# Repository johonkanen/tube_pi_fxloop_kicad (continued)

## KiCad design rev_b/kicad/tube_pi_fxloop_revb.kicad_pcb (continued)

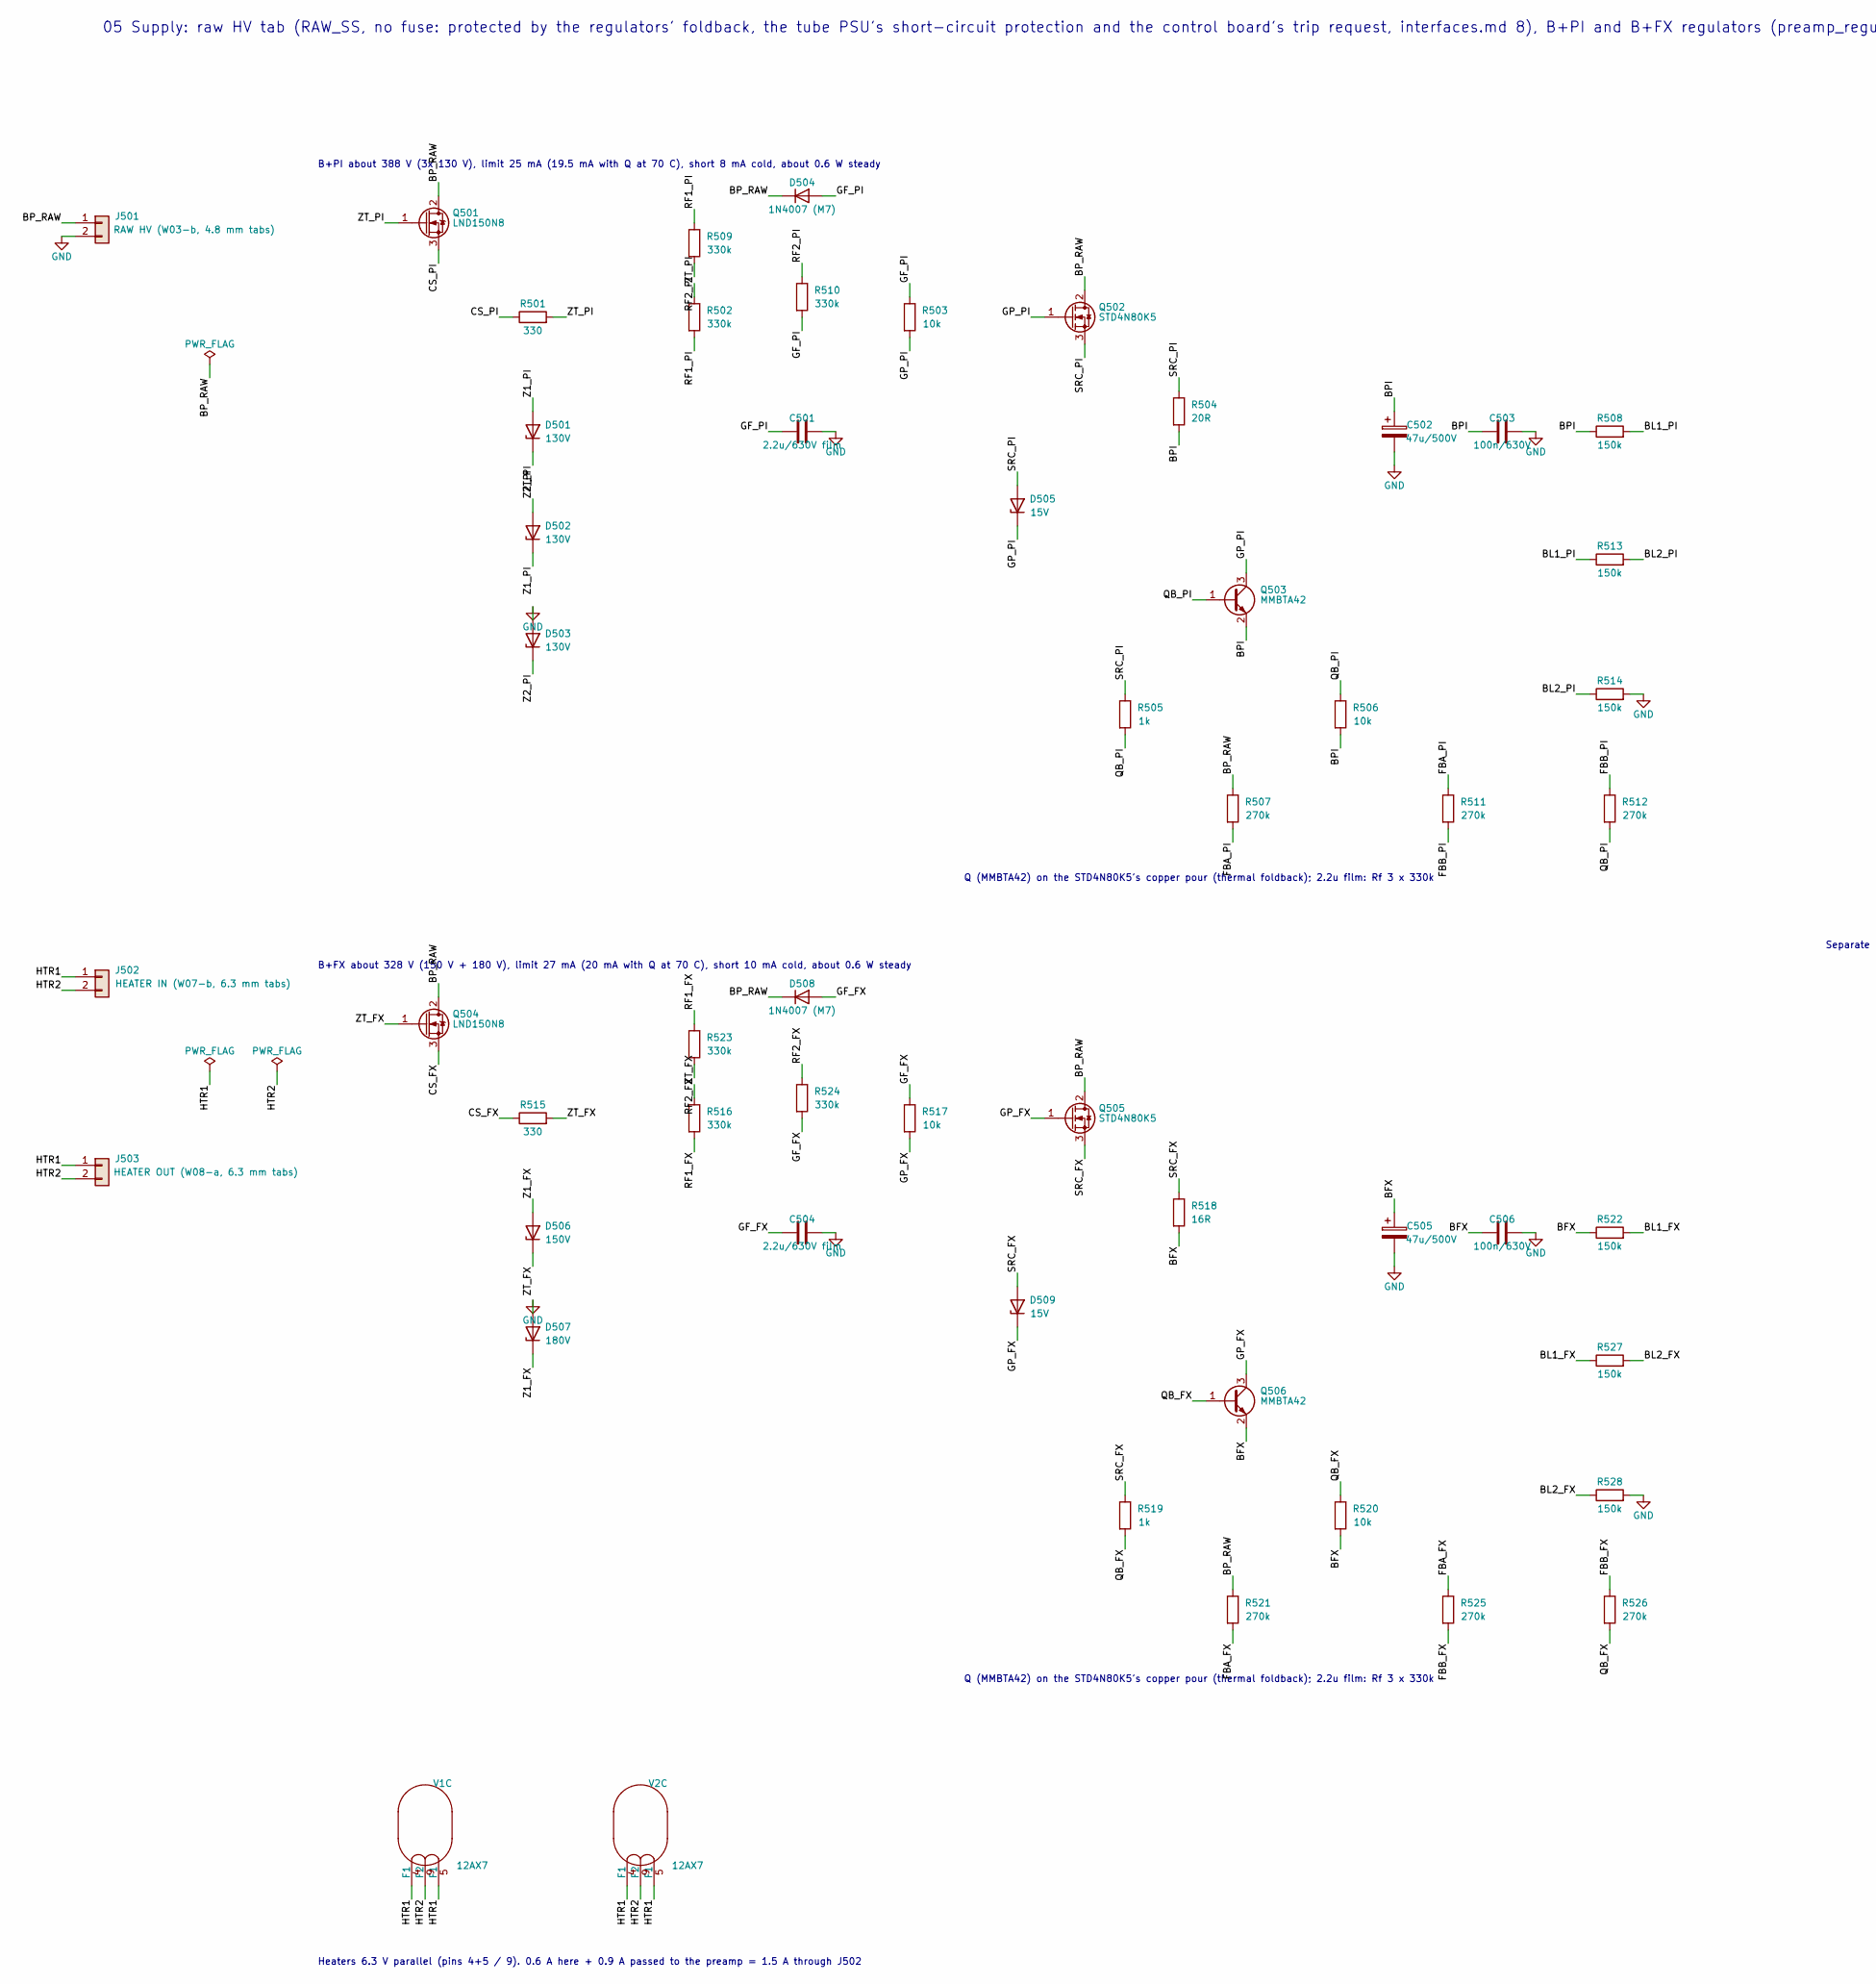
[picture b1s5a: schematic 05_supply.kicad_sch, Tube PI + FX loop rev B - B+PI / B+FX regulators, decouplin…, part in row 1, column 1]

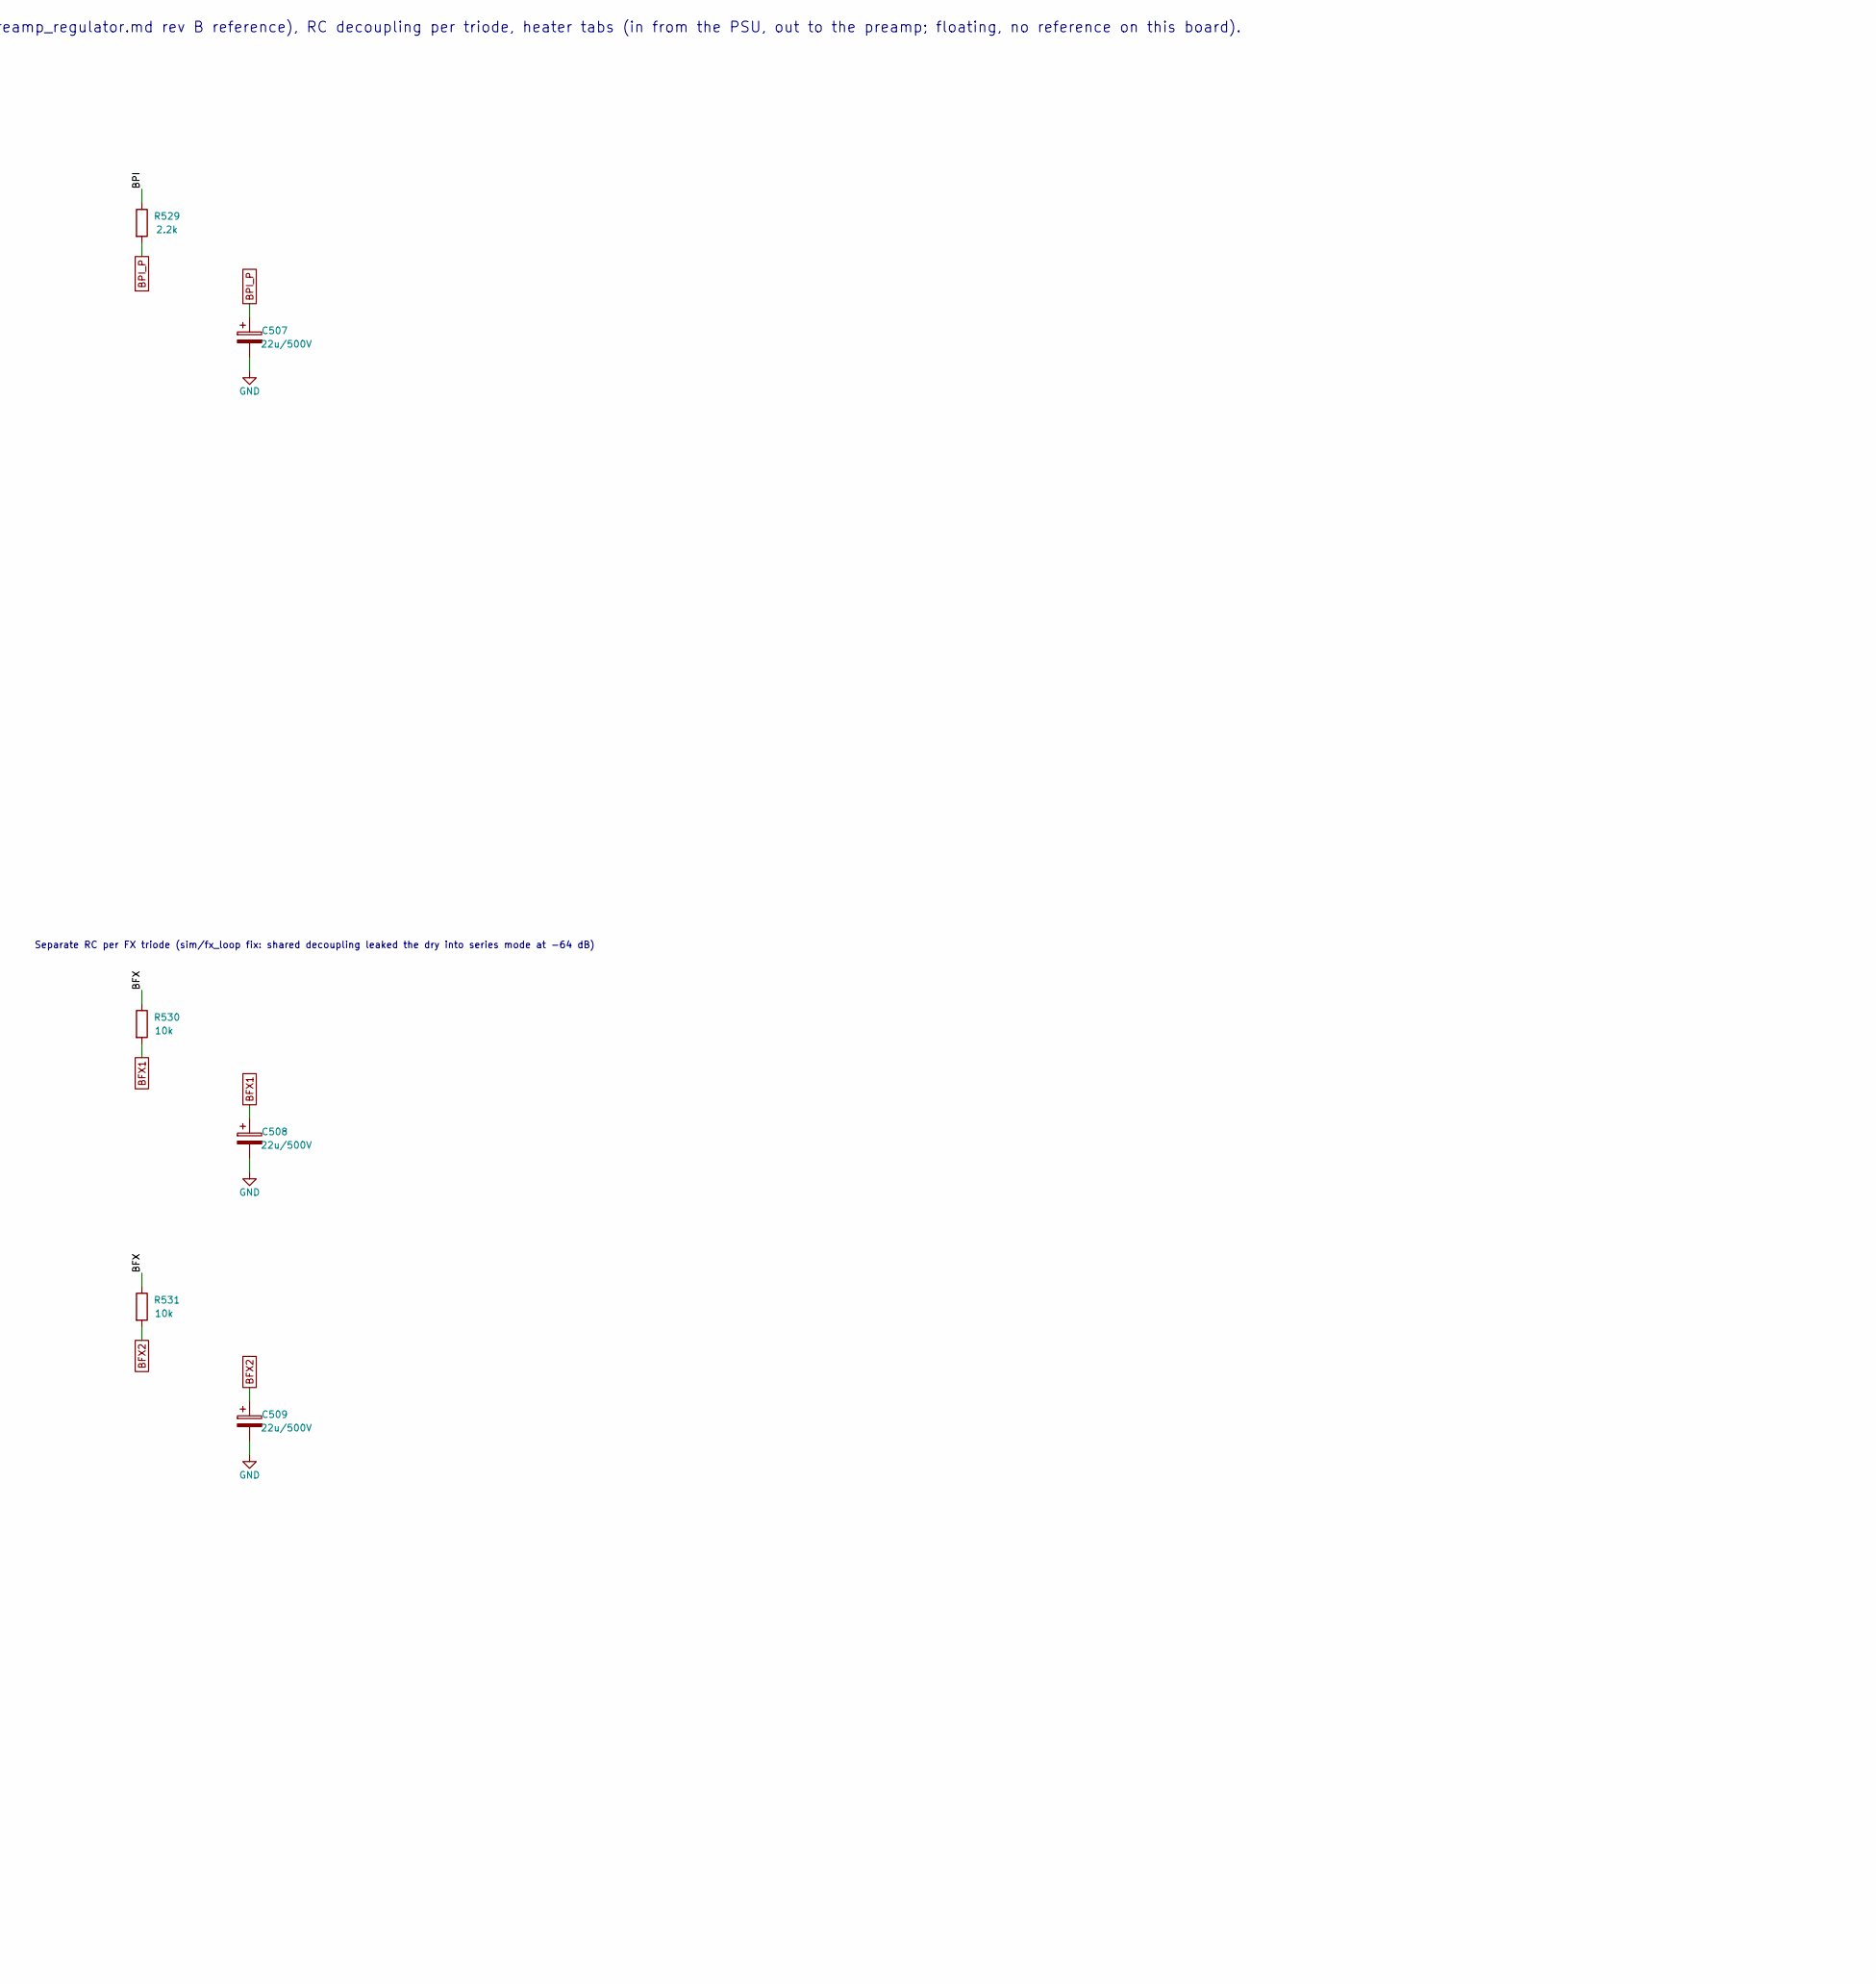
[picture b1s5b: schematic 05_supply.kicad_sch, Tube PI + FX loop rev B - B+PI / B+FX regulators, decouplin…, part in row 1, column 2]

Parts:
C501, C504: 2.2u/630V film; C_Rect_L31.5mm_W17.0mm_P27.50mm_MKS4
C502, C505: 47u/500V; CP_Radial_D18.0mm_P7.50mm
C503, C506: 100n/630V; C_Rect_L13.0mm_W5.0mm_P10.00mm_FKS3_FKP3_MKS4
C507, C508, C509: 22u/500V; CP_Radial_D16.0mm_P7.50mm
D501, D502, D503: 130V; D_SMA
D504, D508: 1N4007 (M7); D_SMA
D505, D509: 15V; D_SOD-123
D506: 150V; D_SMA
D507: 180V; D_SMA
J501: RAW HV (W03-b, 4.8 mm tabs); Faston_Tab_4.8mm_x2_P15.00mm
J502: HEATER IN (W07-b, 6.3 mm tabs); Faston_Tab_6.3mm_x2_P12.70mm
J503: HEATER OUT (W08-a, 6.3 mm tabs); Faston_Tab_6.3mm_x2_P12.70mm
Q501, Q504: LND150N8; SOT-89-3
Q502, Q505: STD4N80K5; TO-252-2
Q503, Q506: MMBTA42; SOT-23
R501, R515: 330; R_1206_3216Metric
R502, R509, R510, R516, R523, R524: 330k; R_2512_6332Metric
R503, R506, R517, R520, R530, R531: 10k; R_1206_3216Metric
R504: 20R; R_1206_3216Metric
R505, R519: 1k; R_1206_3216Metric
R507, R511, R512, R521, R525, R526: 270k; R_2512_6332Metric
R508, R513, R514, R522, R527, R528: 150k; R_2512_6332Metric
R518: 16R; R_1206_3216Metric
R529: 2.2k; R_1206_3216Metric
V1: 12AX7; Valve_Noval_Belton_PCD21.00mm
V2: 12AX7; Valve_Noval_Belton_PCD21.00mm_Pin6_3.8mm

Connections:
/05 B+PI and B+FX regulators, decoupling, heaters, power tabs/BFX: C505.1, C506.1, Q506.2 (E), R518.2, R520.2, R522.1, R530.1, R531.1
/05 B+PI and B+FX regulators, decoupling, heaters, power tabs/BL1_FX: R522.2, R527.1
/05 B+PI and B+FX regulators, decoupling, heaters, power tabs/BL1_PI: R508.2, R513.1
/05 B+PI and B+FX regulators, decoupling, heaters, power tabs/BL2_FX: R527.2, R528.1
/05 B+PI and B+FX regulators, decoupling, heaters, power tabs/BL2_PI: R513.2, R514.1
/05 B+PI and B+FX regulators, decoupling, heaters, power tabs/BPI: C502.1, C503.1, Q503.2 (E), R504.2, R506.2, R508.1, R529.1
/05 B+PI and B+FX regulators, decoupling, heaters, power tabs/BP_RAW: D504.1 (K), D508.1 (K), J501.1, Q501.2 (D), Q502.2 (D), Q504.2 (D), Q505.2 (D), R507.1, R521.1
/05 B+PI and B+FX regulators, decoupling, heaters, power tabs/CS_FX: Q504.3 (S), R515.1
/05 B+PI and B+FX regulators, decoupling, heaters, power tabs/CS_PI: Q501.3 (S), R501.1
/05 B+PI and B+FX regulators, decoupling, heaters, power tabs/FBA_FX: R521.2, R525.1
/05 B+PI and B+FX regulators, decoupling, heaters, power tabs/FBA_PI: R507.2, R511.1
/05 B+PI and B+FX regulators, decoupling, heaters, power tabs/FBB_FX: R525.2, R526.1
/05 B+PI and B+FX regulators, decoupling, heaters, power tabs/FBB_PI: R511.2, R512.1
/05 B+PI and B+FX regulators, decoupling, heaters, power tabs/GF_FX: C504.1, D508.2 (A), R517.1, R524.2
/05 B+PI and B+FX regulators, decoupling, heaters, power tabs/GF_PI: C501.1, D504.2 (A), R503.1, R510.2
/05 B+PI and B+FX regulators, decoupling, heaters, power tabs/GP_FX: D509.1 (K), Q505.1 (G), Q506.3 (C), R517.2
/05 B+PI and B+FX regulators, decoupling, heaters, power tabs/GP_PI: D505.1 (K), Q502.1 (G), Q503.3 (C), R503.2
/05 B+PI and B+FX regulators, decoupling, heaters, power tabs/HTR1: J502.1, J503.1, V1.4 (F1), V1.5 (F1), V2.4 (F1), V2.5 (F1)
/05 B+PI and B+FX regulators, decoupling, heaters, power tabs/HTR2: J502.2, J503.2, V1.9 (F2), V2.9 (F2)
/05 B+PI and B+FX regulators, decoupling, heaters, power tabs/QB_FX: Q506.1 (B), R519.2, R520.1, R526.2
/05 B+PI and B+FX regulators, decoupling, heaters, power tabs/QB_PI: Q503.1 (B), R505.2, R506.1, R512.2
/05 B+PI and B+FX regulators, decoupling, heaters, power tabs/RF1_FX: R516.2, R523.1
/05 B+PI and B+FX regulators, decoupling, heaters, power tabs/RF1_PI: R502.2, R509.1
/05 B+PI and B+FX regulators, decoupling, heaters, power tabs/RF2_FX: R523.2, R524.1
/05 B+PI and B+FX regulators, decoupling, heaters, power tabs/RF2_PI: R509.2, R510.1
/05 B+PI and B+FX regulators, decoupling, heaters, power tabs/SRC_FX: D509.2 (A), Q505.3 (S), R518.1, R519.1
/05 B+PI and B+FX regulators, decoupling, heaters, power tabs/SRC_PI: D505.2 (A), Q502.3 (S), R504.1, R505.1
/05 B+PI and B+FX regulators, decoupling, heaters, power tabs/Z1_FX: D506.2 (A), D507.1 (K)
/05 B+PI and B+FX regulators, decoupling, heaters, power tabs/Z1_PI: D501.2 (A), D502.1 (K)
/05 B+PI and B+FX regulators, decoupling, heaters, power tabs/Z2_PI: D502.2 (A), D503.1 (K)
/05 B+PI and B+FX regulators, decoupling, heaters, power tabs/ZT_FX: D506.1 (K), Q504.1 (G), R515.2, R516.1
/05 B+PI and B+FX regulators, decoupling, heaters, power tabs/ZT_PI: D501.1 (K), Q501.1 (G), R501.2, R502.1
BFX1: C508.1, R530.2; also elsewhere on the board
BFX2: C509.1, R531.2; also elsewhere on the board
BPI_P: C507.1, R529.2; also elsewhere on the board
GND: C501.2, C502.2, C503.2, C504.2, C505.2, C506.2, C507.2, C508.2, C509.2, D503.2 (A), D507.2 (A), J501.2, R514.2, R528.2; also elsewhere on the board

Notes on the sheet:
05 Supply: raw HV tab (RAW_SS, no fuse: protected by the regulators' foldback, the tube PSU's short-circuit protection and the control board's trip request, interfaces.md 8), B+PI and B+FX regulators (preamp_regulator.md rev B reference), RC decoupling per triode, heater tabs (in from the PSU, out 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
B+PI about 388 V (3x 130 V), limit 25 mA (19.5 mA with Q at 70 C), short 8 mA cold, about 0.6 W steady
Q (MMBTA42) on the STD4N80K5's copper pour (thermal foldback); 2.2u film: Rf 3 x 330k
B+FX about 328 V (150 V + 180 V), limit 27 mA (20 mA with Q at 70 C), short 10 mA cold, about 0.6 W steady
Separate RC per FX triode (sim/fx_loop fix: shared decoupling leaked the dry into series mode at -64 dB)
Heaters 6.3 V parallel (pins 4+5 / 9). 0.6 A here + 0.9 A passed to the preamp = 1.5 A through J502

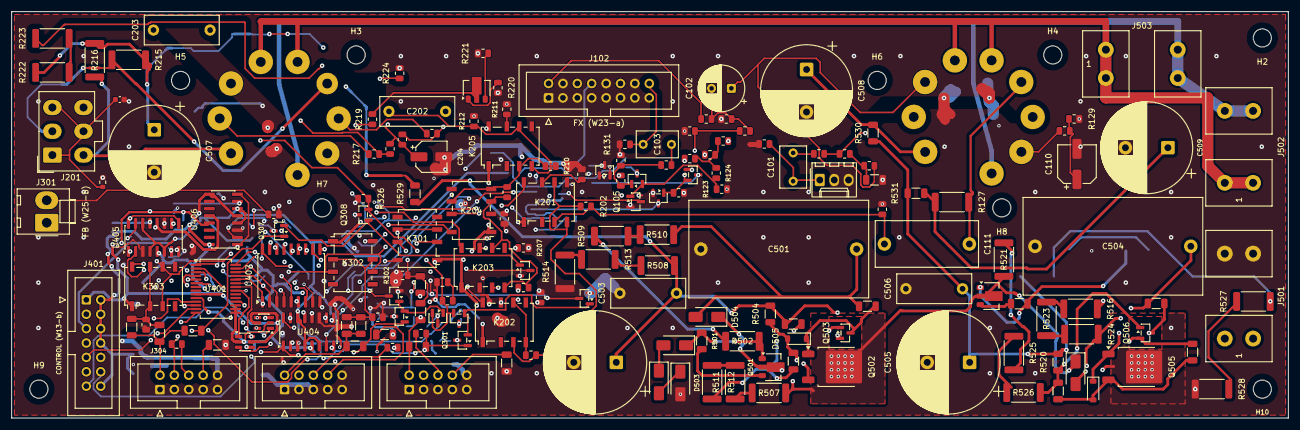
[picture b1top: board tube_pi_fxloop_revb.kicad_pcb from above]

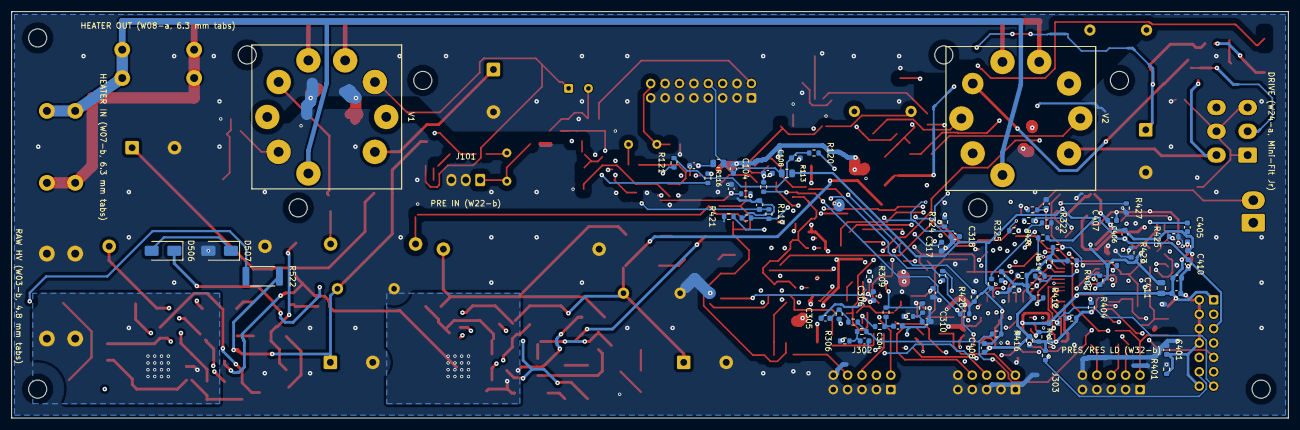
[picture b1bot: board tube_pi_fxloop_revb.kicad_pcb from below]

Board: 4 copper layers, 225.4 x 71.8 mm, 261 parts (81 on the bottom side), 168 nets.

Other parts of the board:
H2, H3, H4, H5, H6, H7, H8, H9, H10: M3 (3.2 NPTH, no net); MountingHole_3.2mm_M3

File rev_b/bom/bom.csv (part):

Qty,Refs,Value,Footprint,Candidate MPN,LCSC,DNP,Note
1,C101,100n/250V film,Capacitor_THT:C_Rect_L7.2mm_W4.5mm_P5.00mm_FKS2_FKP2_MKS2_MKP2,,,,film >= 100 V (PET / PP)
1,C102,4.7u/160V,Capacitor_THT:CP_Radial_D8.0mm_P3.50mm,,,,105 C electrolytic
1,C103,220n/100V film,Capacitor_THT:C_Rect_L7.2mm_W4.5mm_P5.00mm_FKS2_FKP2_MKS2_MKP2,,,,film >= 100 V (PET / PP)
12,C104 C201 C401 C402 C403 C404 C405 C406 C407 C408 C409 C410,100n,Capacitor_SMD:C_0603_1608Metric,CC0603KRX7R9BB104,C14663,,
14,C105 C106 C107 C108 C109 C304 C305 C306 C310 C311 C312 C316 C317 C318,10n,Capacitor_SMD:C_0603_1608Metric,0603B103K500NT,C57112,,
1,C110,100u/25V,Capacitor_SMD:CP_Elec_6.3x7.7,,,,105 C electrolytic
1,C111,470n/400V film,Capacitor_THT:C_Rect_L18.0mm_W8.0mm_P15.00mm_FKS3_FKP3,CBB21-400V474JP15,C2888194,,film >= 400 V
1,C202,10n/630V film,Capacitor_THT:C_Rect_L13.0mm_W5.0mm_P10.00mm_FKS3_FKP3_MKS4,,,,film 630 V
1,C203,22n/630V film,Capacitor_THT:C_Rect_L13.0mm_W5.0mm_P10.00mm_FKS3_FKP3_MKS4,MPE223J2JB050C030ZR,C53224144,,film 630 V
1,C204,10u/50V,Capacitor_SMD:CP_Elec_5x5.4,,,,105 C electrolytic
3,C301 C307 C313,22p/200V C0G (PI-6),Capacitor_SMD:C_1206_3216Metric,,,,
6,C302 C303 C308 C309 C314 C315,22n C0G 50V,Capacitor_SMD:C_1206_3216Metric,C1206N223K050T,C105982,,
1,C319,DNP (step C),Capacitor_SMD:C_0805_2012Metric,,,yes,
1,C411,10u/16V,Capacitor_SMD:C_0805_2012Metric,,,,
2,C501 C504,2.2u/630V film,Capacitor_THT:C_Rect_L31.5mm_W17.0mm_P27.50mm_MKS4,,,,PP film 630 V (preamp_regulator.md)
2,C502 C505,47u/500V,Capacitor_THT:CP_Radial_D18.0mm_P7.50mm,"Nichicon UCY2H470MHD6 (18 x 31.5, P7.5; alt. Rubycon 500LXW47MEFR18X25)",,,"105 C, 12000 h, not at LCSC: hand-solder"
2,C503 C506,100n/630V,Capacitor_THT:C_Rect_L13.0mm_W5.0mm_P10.00mm_FKS3_FKP3_MKS4,CBB21-630V104JP10,C2888191,,film 630 V
3,C507 C508 C509,22u/500V,Capacitor_THT:CP_Radial_D16.0mm_P7.50mm,"Nichicon UCY2H220MHD6 (16 x 25, P7.5)",,,"105 C, 12000 h, not at LCSC: hand-solder"
3,D501 D502 D503,130V,Diode_SMD:D_SMA,1SMA5952B,C48578686,,
2,D504 D508,1N4007 (M7),Diode_SMD:D_SMA,M7,C7420350,,
2,D505 D509,15V,Diode_SMD:D_SOD-123,BZT52C15,C2891782,,
1,D506,150V,Diode_SMD:D_SMA,1SMA5953B,,,
1,D507,180V,Diode_SMD:D_SMA,1SMA5955B,,,
1,J101,PRE IN (W22-b),Connector_Molex:Molex_KK-254_AE-6410-03A_1x03_P2.54mm_Vertical,Molex 22272031,C471416,,
1,J102,FX (W23-a),Connector_IDC:IDC-Header_2x08_P2.54mm_Vertical,,,,
1,J201,"DRIVE (W24-a, Mini-Fit Jr)",Connector_Molex:Molex_Mini-Fit_Jr_5566-06A_2x03_P4.20mm_Vertical,"Molex 39-28-1063 class (5566-06A; confirm the order code), receptacle 39-01-2060",,,"W24: Mini-Fit Jr 600 V (V5); 2x3 with position 6 unused, same mapping on the power amp"
1,J301,FB (W25-b),Connector_Molex:Molex_KK-396_A-41791-0002_1x02_P3.96mm_Vertical,,,,
1,J302,PRES/RES CL (W30-b),Connector_IDC:IDC-Header_2x05_P2.54mm_Vertical,,,,
1,J303,PRES/RES CR (W31-b),Connector_IDC:IDC-Header_2x05_P2.54mm_Vertical,,,,
1,J304,PRES/RES LD (W32-b),Connector_IDC:IDC-Header_2x05_P2.54mm_Vertical,,,,
1,J401,CONTROL (W13-b),Connector_IDC:IDC-Header_2x07_P2.54mm_Vertical,HY2541WV-N-2x7P,C17179454,,
1,J501,"RAW HV (W03-b, 4.8 mm tabs)",tube_pi_fxloop_revb:PLACEHOLDER_Tab_x2_4.8mm_Legs_P5.00mm_D1.4mm,2x BTC-3-PCB484608T,C20626099,,PLACEHOLDER footprint
1,J502,"HEATER IN (W07-b, 6.3 mm tabs)",tube_pi_fxloop_revb:PLACEHOLDER_Tab_x2_6.3mm_Legs_P5.00mm_D1.4mm,2x BTC-3-PCB485005D,C20626100,,PLACEHOLDER footprint
1,J503,"HEATER OUT (W08-a, 6.3 mm tabs)",tube_pi_fxloop_revb:PLACEHOLDER_Tab_x2_6.3mm_Legs_P5.00mm_D1.4mm,2x BTC-3-PCB485005D,C20626100,,PLACEHOLDER footprint
8,K201 K202 K203 K204 K205 K301 K302 K303,G6K-2F-Y 5VDC,Relay_SMD:Relay_DPDT_Omron_G6K-2F-Y,G6K-2F-Y-TR DC5,C47190,,"coil + 1 / - 8; NC 4 / 5, NO 2 / 7 (Omron datasheet)"
14,Q101 Q102 Q103 Q104 Q105 Q301 Q302 Q303 Q304 Q305 Q306 Q307 Q308 Q309,MMBFJ113,Package_TO_SOT_SMD:SOT-23,MMBFJ113,C891686,,
1,Q201,DN2540N8,Package_TO_SOT_SMD:SOT-89-3,DN2540N8-G,,,
2,Q501 Q504,LND150N8,Package_TO_SOT_SMD:SOT-89-3,LND150N8-G,C629123,,
2,Q502 Q505,STD4N80K5,Package_TO_SOT_SMD:TO-252-2,STD4N80K5,C472540,,DPAK on a copper pour; Q MMBTA42 on the same pour (thermal foldback)
2,Q503 Q506,MMBTA42,Package_TO_SOT_SMD:SOT-23,MMBTA42,C20069138,,
2,R101 R131,2.2M,Resistor_SMD:R_0805_2012Metric,0805W8F2204T5E,,,
3,R102 R109 R326,4.7k,Resistor_SMD:R_0805_2012Metric,0805W8F4701T5E,,,
12,R103 R106 R111 R113 R118 R123 R130 R213 R218 R302 R310 R318,1M,Resistor_SMD:R_0805_2012Metric,0805W8F1004T5E,C17514,,
1,R104,1.5k,Resistor_SMD:R_0805_2012Metric,0805W8F1501T5E,,,
1,R105,22k 0.5W,Resistor_SMD:R_1206_3216Metric,1206W4F2202T5E,,,
8,R107 R126 R214 R217 R219 R304 R312 R320,1k,Resistor_SMD:R_0805_2012Metric,0805W8F1001T5E,,,
1,R108,47k,Resistor_SMD:R_0805_2012Metric,0805W8F4702T5E,,,
5,R110 R114 R119 R124 R224,100k,Resistor_SMD:R_0805_2012Metric,0805W8F1003T5E,C149504,,
1,R112,11k,Resistor_SMD:R_0805_2012Metric,0805W8F1102T5E,,,
38,R115 R117 R120 R122 R305 R307 R309 R313 R315 R317 R321 R323 R325 R403 R404 R405 R406 R407 R408 R409 R410 R411 R412 R413 R414 R415 R416 R417 R418 R419 R420 R421 R422 R423 R424 R425 R426 R427,100k,Resistor_SMD:R_0603_1608Metric,0603WAF1003T5E,C25803,,
8,R116 R121 R306 R308 R314 R316 R322 R324,1M,Resistor_SMD:R_0603_1608Metric,0603WAF1004T5E,,,
1,R125,220k,Resistor_SMD:R_0805_2012Metric,0805W8F2203T5E,C17556,,
1,R127,100k,Resistor_SMD:R_2512_6332Metric,FRC2512F1003TS,C2934045,,"2512, 1 W, 200 V"
1,R128,680,Resistor_SMD:R_0805_2012Metric,0805W8F6800T5E,,,
1,R129,820,Resistor_SMD:R_0805_2012Metric,0805W8F8200T5E,,,
2,R201 R401,10R,Resistor_SMD:R_0603_1608Metric,0603WAF100JT5E,C22859,,
1,R202,5.36k,Resistor_SMD:R_0805_2012Metric,0805W8F5361T5E,,,
1,R203,412k,Resistor_SMD:R_0805_2012Metric,0805W8F4123T5E,,,
1,R204,10.2k,Resistor_SMD:R_0805_2012Metric,0805W8F1022T5E,,,
1,R205,191k,Resistor_SMD:R_0805_2012Metric,0805W8F1913T5E,,,
1,R206,18.2k,Resistor_SMD:R_0805_2012Metric,0805W8F1822T5E,,,
1,R207,84.5k,Resistor_SMD:R_0805_2012Metric,0805W8F8452T5E,,,
1,R208,30.1k,Resistor_SMD:R_0805_2012Metric,0805W8F3012T5E,,,
1,R209,33.2k,Resistor_SMD:R_0805_2012Metric,0805W8F3322T5E,,,
1,R210,42.2k,Resistor_SMD:R_0805_2012Metric,0805W8F4222T5E,,,
1,R211,7.87k,Resistor_SMD:R_0805_2012Metric,0805W8F7871T5E,,,
1,R212,49.9k,Resistor_SMD:R_0805_2012Metric,0805W8F4992T5E,,,
2,R215 R216,100k 1W,Resistor_SMD:R_2512_6332Metric,25121WF1003T4E,,,"2512, 1 W, 200 V"
1,R220,100,Resistor_SMD:R_0805_2012Metric,0805W8F1000T5E,,,
1,R221,"1k (select, ~2 mA)",Resistor_SMD:R_0805_2012Metric,0805W8F1001T5E,,,
2,R222 R223,820k,Resistor_SMD:R_2512_6332Metric,25121WF8203T4E,,,"2512, 1 W, 200 V"
1,R301,0R,Resistor_SMD:R_0805_2012Metric,0805W8F0000T5E,,,
3,R303 R311 R319,100k 0.5W,Resistor_SMD:R_1206_3216Metric,1206W4F1003T5E,,,
1,R327,DNP (step R),Resistor_SMD:R_0805_2012Metric,,,yes,
1,R402,10k,Resistor_SMD:R_0603_1608Metric,0603WAF1002T5E,C25804,,
2,R501 R515,330,Resistor_SMD:R_1206_3216Metric,FRC1206F3300TS,C2933675,,
6,R502 R509 R510 R516 R523 R524,330k,Resistor_SMD:R_2512_6332Metric,25121WF3303T4E,,,"2512, 1 W, 200 V"
6,R503 R506 R517 R520 R530 R531,10k,Resistor_SMD:R_1206_3216Metric,1206W4F1002T5E,C17902,,
1,R504,20R,Resistor_SMD:R_1206_3216Metric,1206 20R 1 % thick film,,,
2,R505 R519,1k,Resistor_SMD:R_1206_3216Metric,1206W4F1001T5E,C4410,,
6,R507 R511 R512 R521 R525 R526,270k,Resistor_SMD:R_2512_6332Metric,CL2512FN270KB,C48392179,,"2512, 1 W, 200 V"
6,R508 R513 R514 R522 R527 R528,150k,Resistor_SMD:R_2512_6332Metric,25121WF1503T4E,,,"2512, 1 W, 200 V"
1,R518,16R,Resistor_SMD:R_1206_3216Metric,1206 16R 1 % thick film,,,
1,R529,2.2k,Resistor_SMD:R_1206_3216Metric,1206W4F2201T5E,,,
1,U401,MCP23S17-E/SS,Package_SO:SSOP-28_5.3x10.2mm_P0.65mm,MCP23S17-E/SS,C148009,,
2,U402 U403,74LVC1G11,Package_TO_SOT_SMD:SOT-23-6,"74LVC1G11GV,125",,,
3,U404 U405 U406,DG412DY,Package_SO:SOIC-16_3.9x9.9mm_P1.27mm,DG412DY-T1-E3,C553989,,
1,U407,ULN2803A,Package_SO:SOIC-18W_7.5x11.6mm_P1.27mm,ULN2803ADWR,,,check the 70 C design temperature against the bought part's rating (ENV-2)
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
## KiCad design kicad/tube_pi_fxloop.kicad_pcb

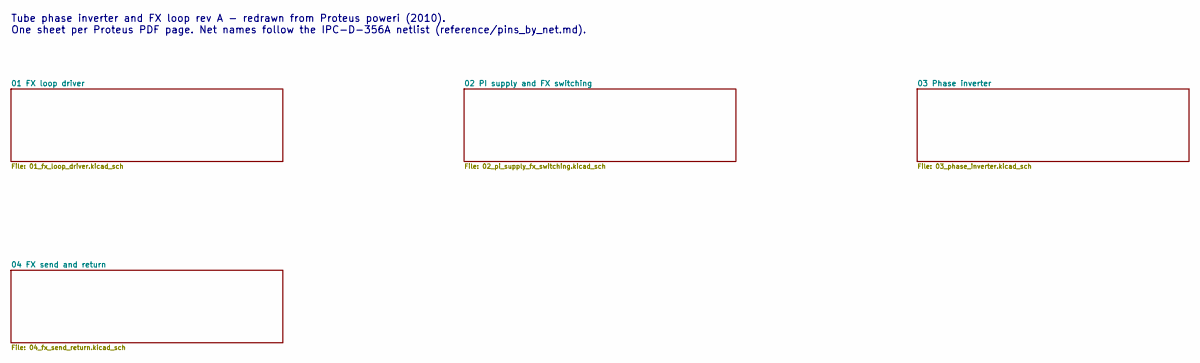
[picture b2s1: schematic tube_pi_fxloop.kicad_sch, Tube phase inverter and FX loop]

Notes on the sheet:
Tube phase inverter and FX loop rev A - redrawn from Proteus poweri (2010). One sheet per Proteus PDF page. Net names follow the IPC-D-356A netlist (reference/pins_by_net.md).

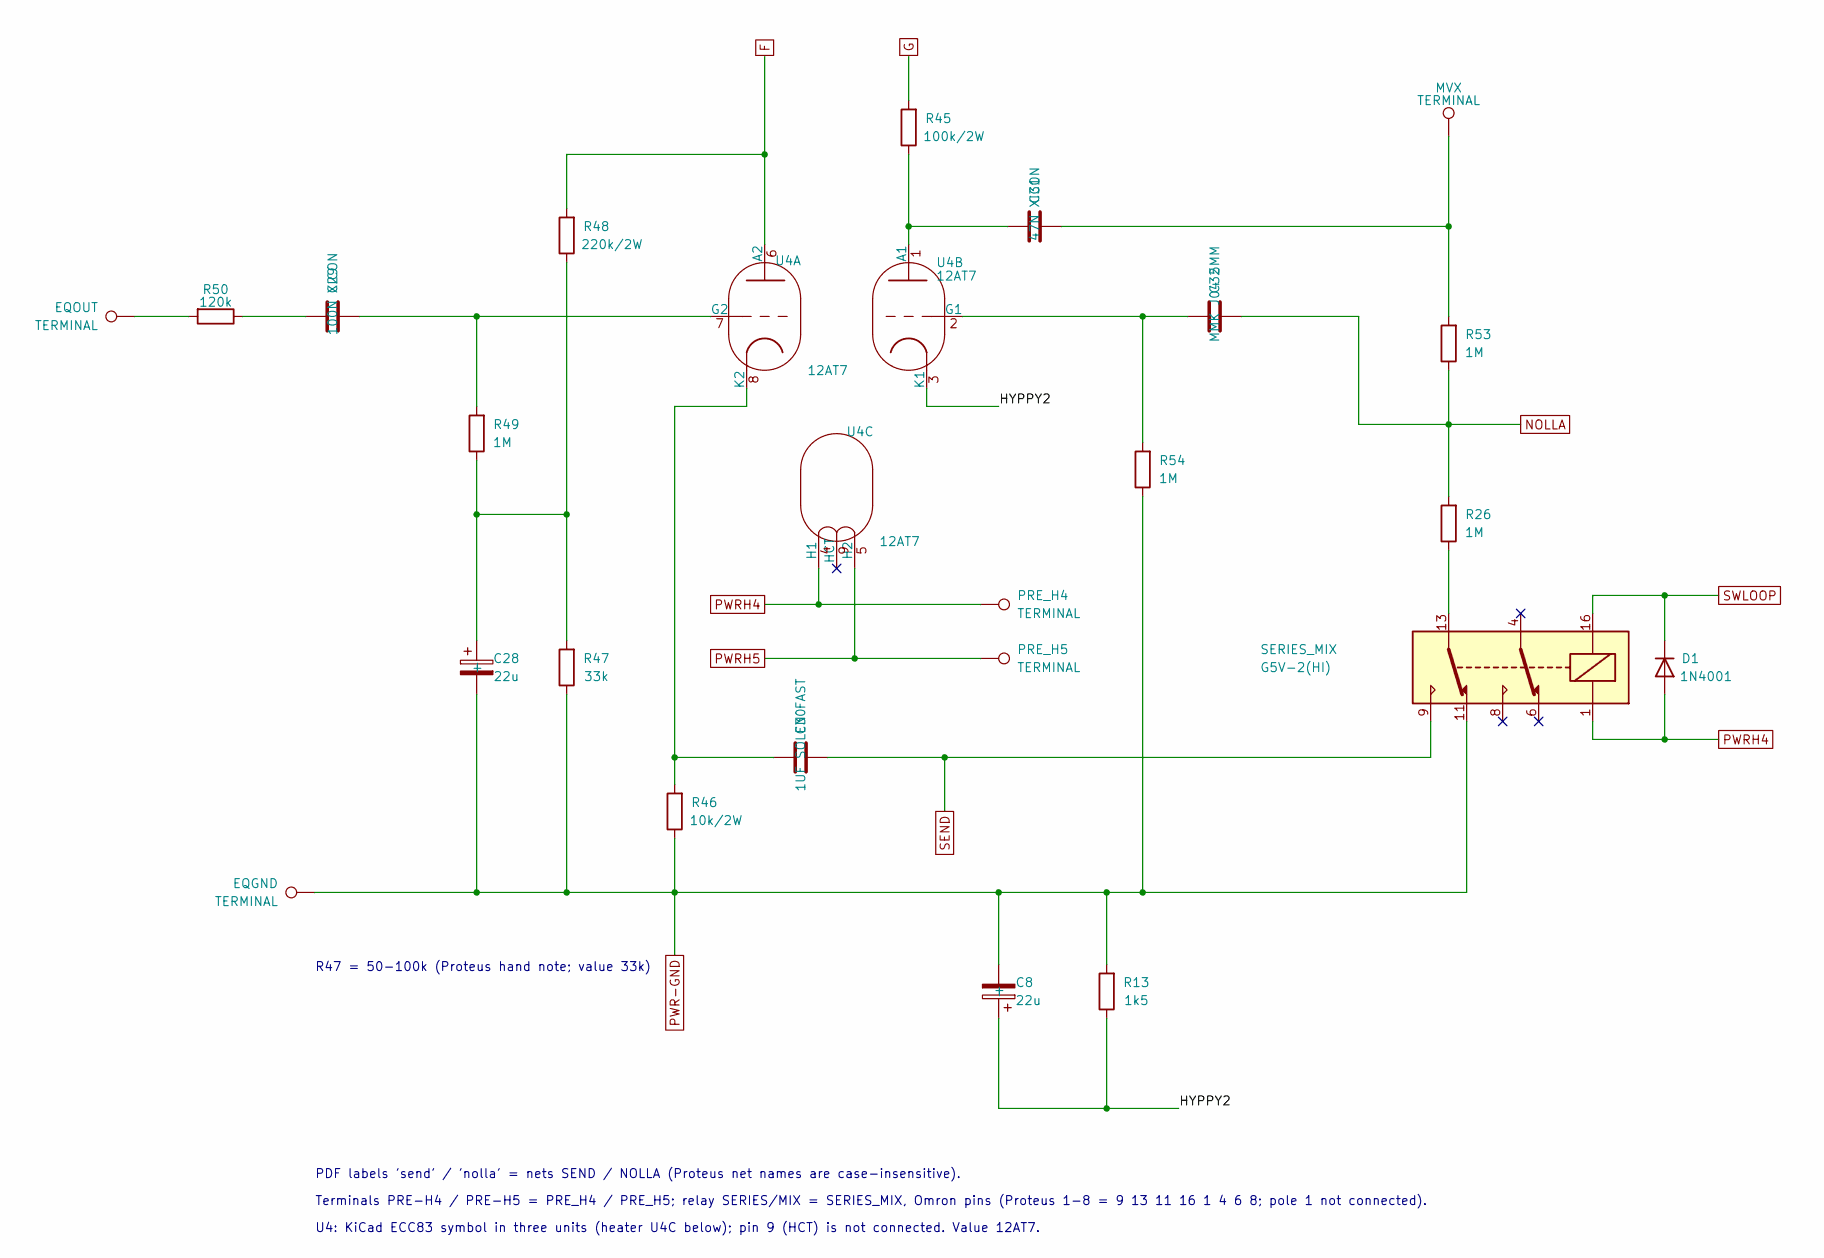
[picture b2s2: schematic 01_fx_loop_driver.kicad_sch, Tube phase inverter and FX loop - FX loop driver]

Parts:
C8, C28: 22u; CP_Radial_D5.0mm_P2.54mm_PM
C29: 100N XICON; C_Rect_L23.1mm_W6.0mm_P20.00mm
C30: 1UF SOLEN FAST; C_Axial_L26.7mm_D15.2mm_P30.48mm_Horizontal
C31: 47N XICON; C_Rect_L18.0mm_W6.0mm_P15.00mm_FKS3_FKP3
C32: MMK J04 5MM; C_Rect_L7.2mm_W5.0mm_P5.00mm
D1: 1N4001; D_DO-41_SOD81_P10.16mm_Horizontal_AK
EQGND: TERMINAL; FlyLead_Pad_D3.048mm_Drill1.524mm
EQOUT: TERMINAL; FlyLead_Pad_D3.048mm_Drill1.524mm
MVX: TERMINAL; FlyLead_Pad_D3.048mm_Drill1.524mm
PRE_H4, PRE_H5: TERMINAL; FlyLead_Pad_D3.048mm_Drill1.524mm
R13: 1k5; R_Axial_DIN0207_L6.3mm_D2.5mm_P10.16mm_Horizontal
R26, R49, R53, R54: 1M; R_Axial_DIN0207_L6.3mm_D2.5mm_P10.16mm_Horizontal
R45: 100k/2W; R_Axial_DIN0414_L11.9mm_D4.5mm_P19.05mm_Horizontal
R46: 10k/2W; R_Axial_DIN0414_L11.9mm_D4.5mm_P19.05mm_Horizontal
R47: 33k; R_Axial_DIN0207_L6.3mm_D2.5mm_P10.16mm_Horizontal
R48: 220k/2W; R_Axial_DIN0414_L11.9mm_D4.5mm_P19.05mm_Horizontal
R50: 120k; R_Axial_DIN0207_L6.3mm_D2.5mm_P10.16mm_Horizontal
SERIES_MIX: G5V-2(HI); Relay_DPDT_Omron_G5V-2
U4: 12AT7; Valve_Noval_Belton_PCD21.00mm

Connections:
/01 FX loop driver/HYPPY2: C8.+, R13.1, U4.3 (K1)
F: R48.2, U4.6 (A2); also elsewhere on the board
G: R45.2; also elsewhere on the board
NOLLA: C32.2, R26.2, R53.1; also elsewhere on the board
unnamed: C28.+, R47.2, R48.1, R49.1
unnamed: C29.1, R50.1
unnamed: C31.2, MVX.1, R53.2
unnamed: EQOUT.1, R50.2
unnamed: R26.1, SERIES_MIX.13
unnamed: C29.2, R49.2, U4.7 (G2)
unnamed: C30.1, R46.2, U4.8 (K2)
unnamed: C31.1, R45.1, U4.1 (A1)
unnamed: C32.1, R54.2, U4.2 (G1)
PWR-GND: C8.-, C28.-, EQGND.1, R13.2, R46.1, R47.1, R54.1, SERIES_MIX.11; also elsewhere on the board
PWRH4: D1.A, PRE_H4.1, SERIES_MIX.1, U4.4 (H1); also elsewhere on the board
PWRH5: PRE_H5.1, U4.5 (H2); also elsewhere on the board
SEND: C30.2, SERIES_MIX.9; also elsewhere on the board
SWLOOP: D1.K, SERIES_MIX.16; also elsewhere on the board

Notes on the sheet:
R47 = 50-100k (Proteus hand note; value 33k)
PDF labels 'send' / 'nolla' = nets SEND / NOLLA (Proteus net names are case-insensitive).
Terminals PRE-H4 / PRE-H5 = PRE_H4 / PRE_H5; relay SERIES/MIX = SERIES_MIX, Omron pins (Proteus 1-8 = 9 13 11 16 1 4 6 8; pole 1 not connected).
U4: KiCad ECC83 symbol in three units (heater U4C below); pin 9 (HCT) is not connected. Value 12AT7.
